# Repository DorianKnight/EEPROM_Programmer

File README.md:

# EEPROM_Programmer

## Project Overview
Custom Serializer Deserializer (SerDes) PCB designed to handle read/write operations to a parallel address EEPROM.

## High Level Architecture
Data from the host computer is transferred through serial communication to the Arduino. The Arduino writes the serial data into the SerDes which outputs the data in parallel to the EEPROM for storage.

To read information from the EEPROM, the Arduino loads the parallel data output into the SerDes and reconstructs the byte packet bit by bit. A high level functional block diagram explaining the system can be seen below.
.png)
.png)

## SerDes
A custom shift register functions as a primitive SerDes. Going from serial to parallel, the custom hardware allows serial data to ripple into individual flip-flops where each flip-flop drives an individual output. These outputs then wire into the EEPROM’s address and data pins. The same hardware also functions to load in the parallel data output from the EEPROM and shift it out sequentially such that the Arduino can reconstruct the byte packet.

## Debugging
To facilitate debugging operations, a debug daughter board PCB was constructed that allows the technician to manually toggle all control signals made available to the Arduino MCU.

## Motherboard Interface
The motherboard hosts a series of LEDs and seven-segment displays that serve to display the byte stored at a specific address. By changing the board to debug mode, the technician can select an address to read its binary and hexadecimal representation.

## Custom Bin -> Hex 7-SD Driver 
Binary to hexadecimal conversion was accomplished through the design of custom digital combinational logic that uses a series of primitive logic gates to turn a four bit binary input into a seven pin output. The individual outputs turn on or off the individual segments on a seven segment display.

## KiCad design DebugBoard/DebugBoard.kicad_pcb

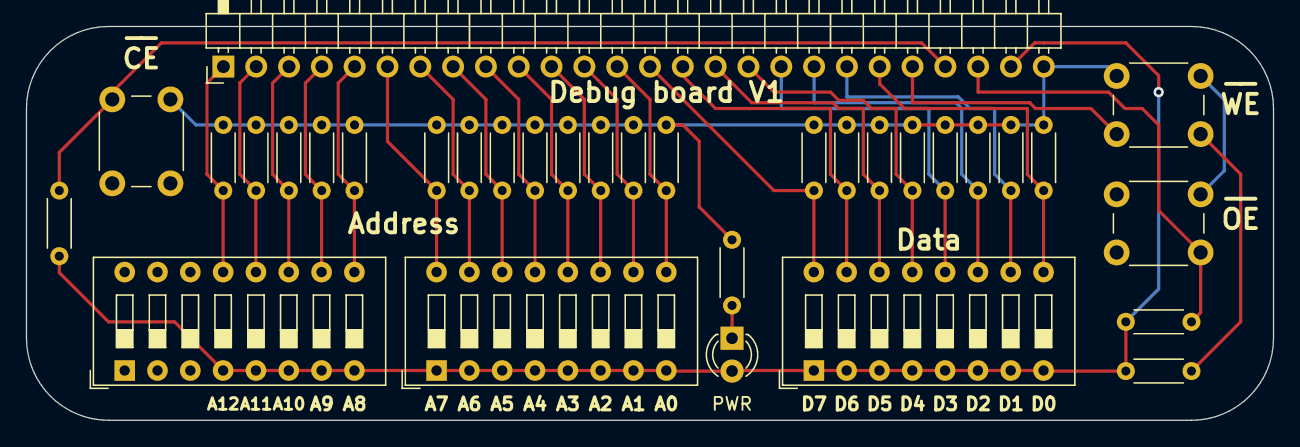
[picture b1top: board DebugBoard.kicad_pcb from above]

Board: 2 copper layers, 96.5 x 30.5 mm, 33 parts (0 on the bottom side), 27 nets.

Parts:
D1: LED; LED_D3.0mm_white
J1: Conn_01x26; PinHeader_1x26_P2.54mm_Horizontal
R1, R2, R3, R4, R5, R6, R7, R8, R9, R10, R11, R12, R13, R14, R15, R16, R17, R18, R19, R20, R21, R22, R23, R24, R25: R_US; R_Axial_DIN0204_L3.6mm_D1.6mm_P5.08mm_Horizontal
SW1, SW2, SW3: SW_DIP_x08; SW_DIP_SPSTx08_Slide_9.78x22.5mm_W7.62mm_P2.54mm
SW4, SW5, SW6: SW_Push; SW_PUSH_6mm

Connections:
A0: J1.13, R24.1, SW3.9
A1: J1.12, R23.1, SW3.10
A2: J1.11, R22.1, SW3.11
A3: J1.10, R21.1, SW3.12
A4: J1.9, R20.1, SW3.13
A5: J1.8, R19.1, SW3.14
A6: J1.7, R18.1, SW3.15
A7: J1.6, R17.1, SW3.16
A8: J1.5, R16.1, SW2.9
A9: J1.4, R15.1, SW2.10
A10: J1.3, R14.1, SW2.11
A11: J1.2, R13.1, SW2.12
A12: J1.1, R12.1, SW2.13
CE': J1.23, R5.2, SW5.2
D0: J1.21, R11.1, SW1.9
D1: J1.20, R10.1, SW1.10
D2: J1.19, R9.1, SW1.11
D3: J1.18, R8.1, SW1.12
D4: J1.17, R6.1, SW1.13
D5: J1.16, R4.1, SW1.14
D6: J1.15, R2.1, SW1.15
D7: J1.14, R1.1, SW1.16
GND: J1.26, R1.2, R2.2, R4.2, R6.2, R8.2, R9.2, R10.2, R11.2, R12.2, R13.2, R14.2, R15.2, R16.2, R17.2, R18.2, R19.2, R20.2, R21.2, R22.2, R23.2, R24.2, R25.1, SW4.1, SW5.1, SW6.1
unnamed: D1.1 (K), R25.2
OE': J1.24, R3.2, SW6.2
VCC: D1.2 (A), J1.25, R3.1, R5.1, R7.1, SW1.1, SW1.2, SW1.3, SW1.4, SW1.5, SW1.6, SW1.7, SW1.8, SW2.4, SW2.5, SW2.6, SW2.7, SW2.8, SW3.1, SW3.2, SW3.3, SW3.4, SW3.5, SW3.6, SW3.7, SW3.8
WE': J1.22, R7.2, SW4.2

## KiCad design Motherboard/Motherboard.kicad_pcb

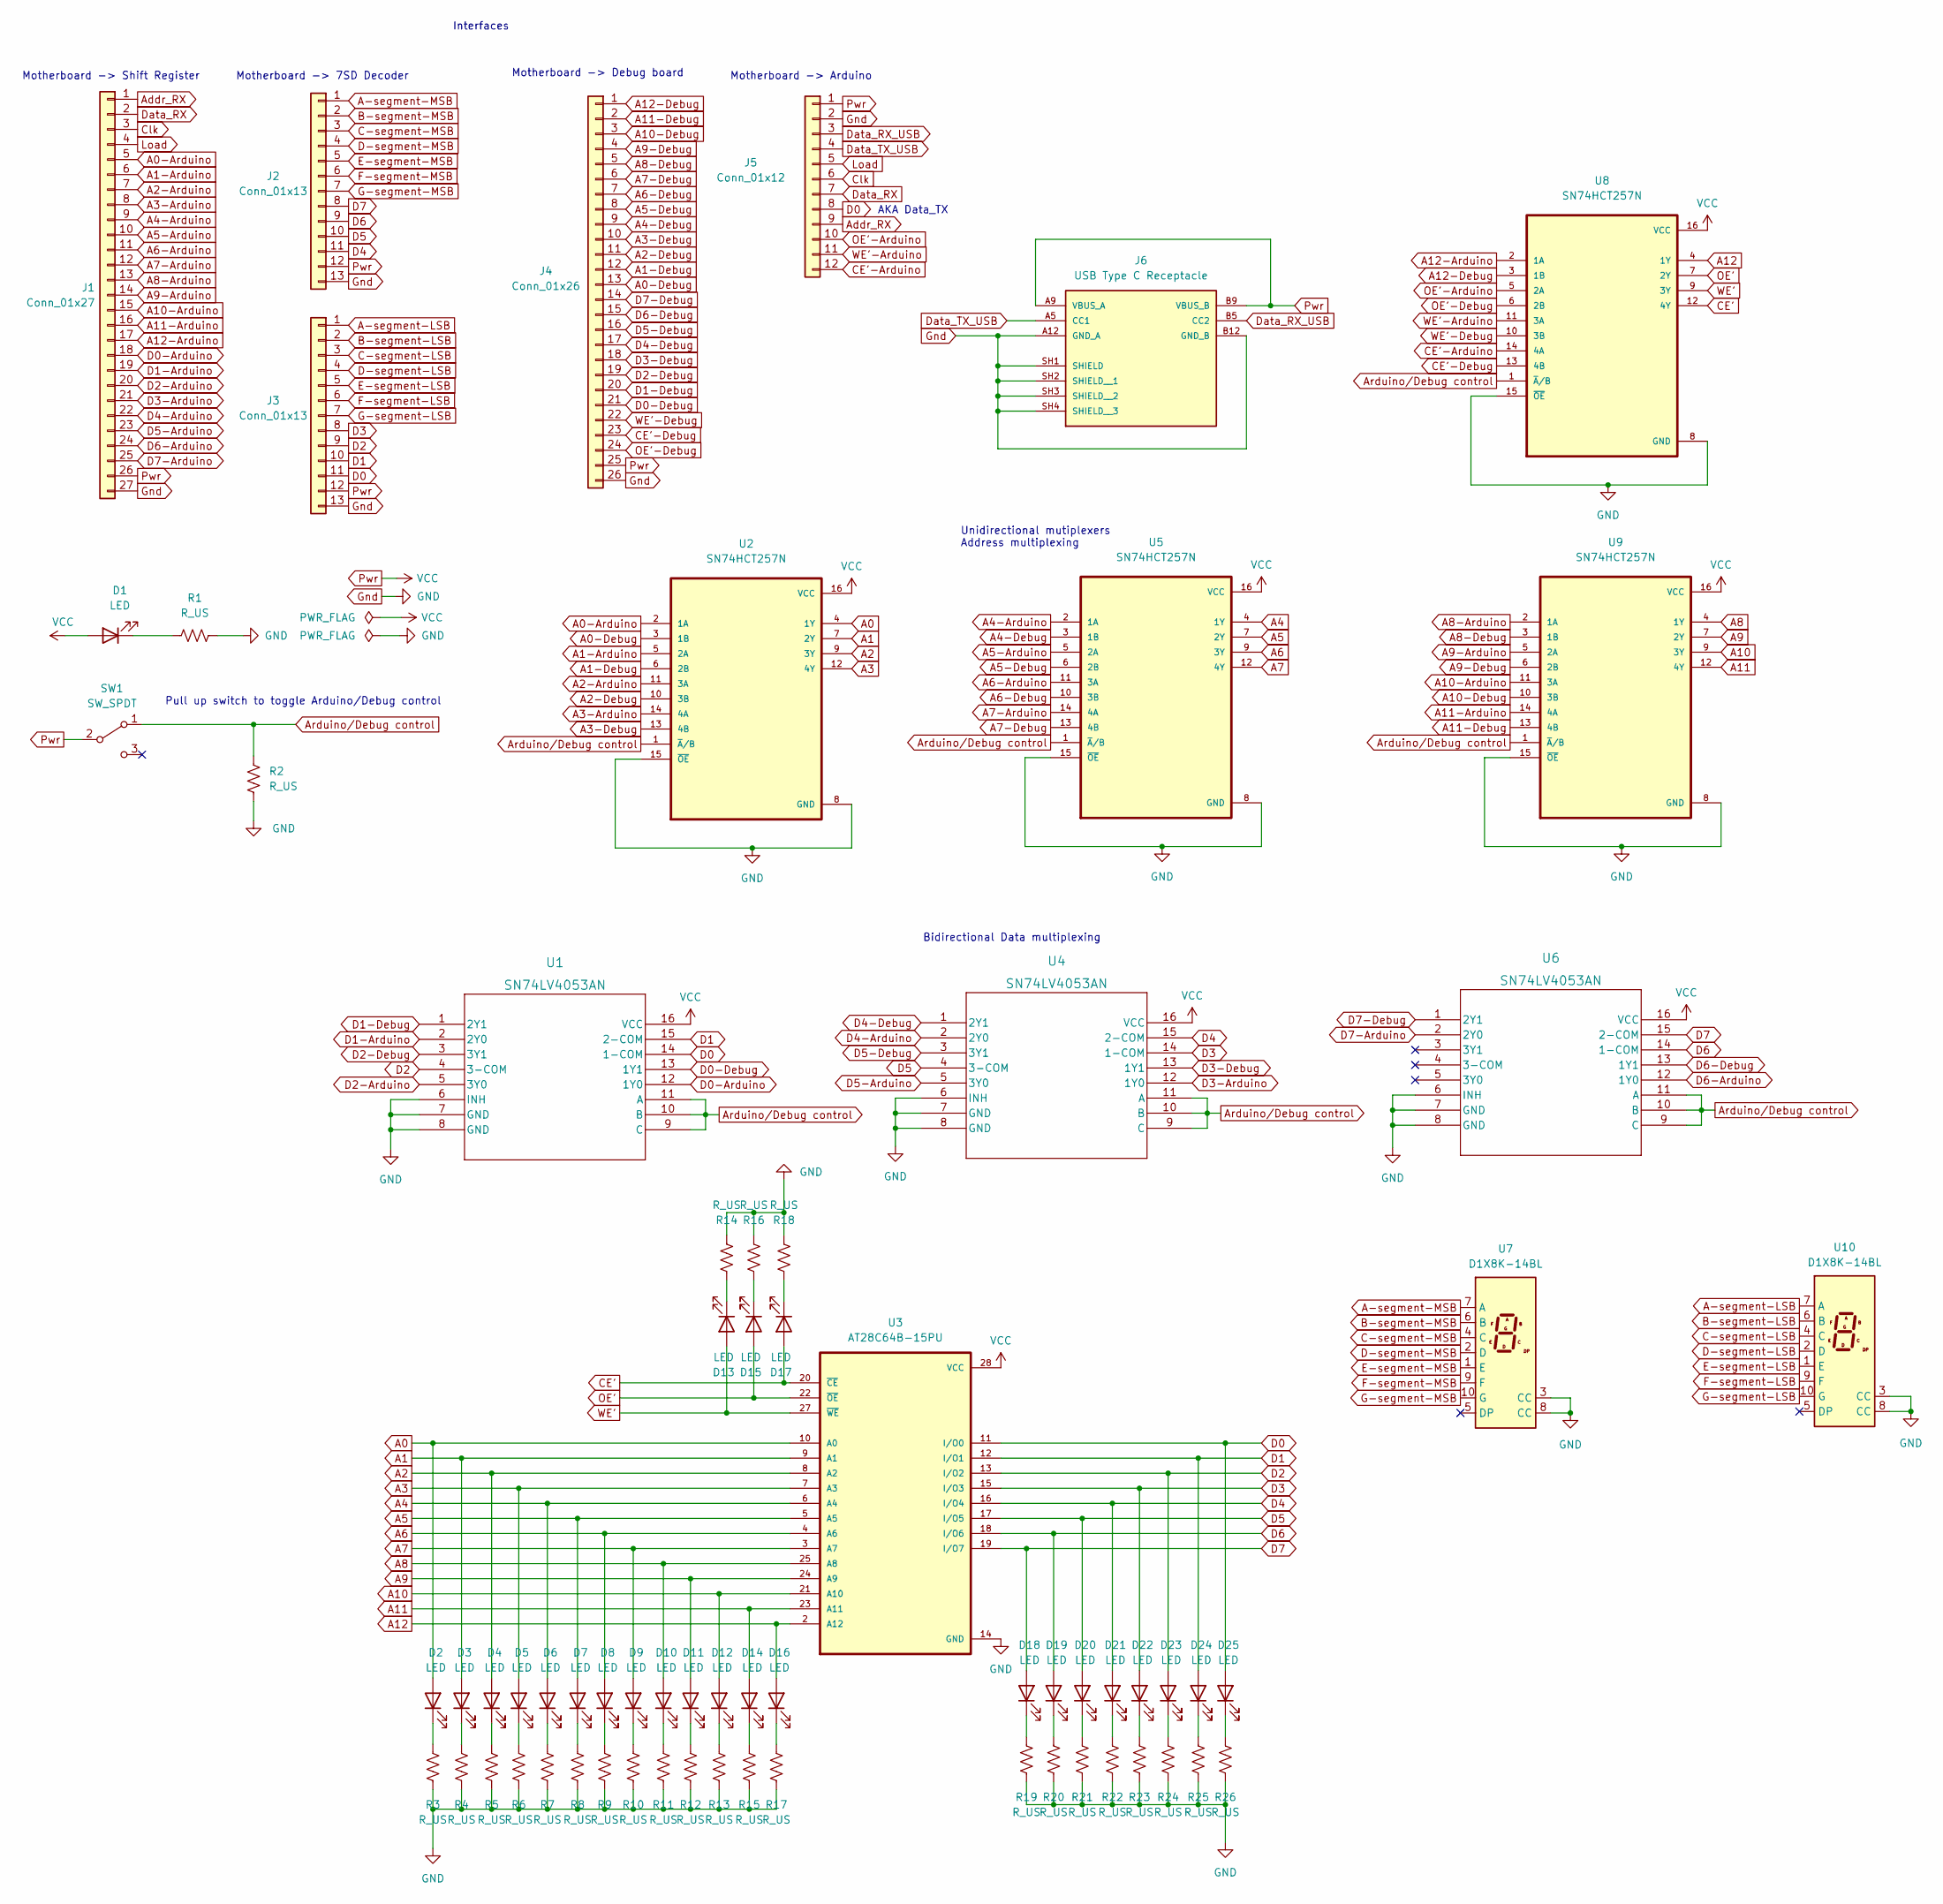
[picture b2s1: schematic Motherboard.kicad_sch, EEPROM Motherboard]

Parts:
D1: LED; LED_D3.0mm_red
D2, D3, D4, D5, D6, D7, D8, D9, D10, D11, D12, D14, D16: LED; LED_D3.0mm_blue
D13, D15, D17: LED; LED_D3.0mm_yellow
D18, D19, D20, D21, D22, D23, D24, D25: LED; LED_D3.0mm_white
J1: Conn_01x27; PinSocket_1x27_P2.54mm_Horizontal
J2, J3: Conn_01x13; PinSocket_1x13_P2.54mm_Horizontal
J4: Conn_01x26; PinSocket_1x26_P2.54mm_Horizontal
J5: Conn_01x12; PinSocket_1x12_P2.54mm_Horizontal
J6: USB Type C Receptacle; AMPHENOL_10164359-00011LF; PARTREV A
R1, R2, R3, R4, R5, R6, R7, R8, R9, R10, R11, R12, R13, R14, R15, R16, R17, R18, R19, R20, R21, R22, R23, R24, R25, R26: R_US; R_Axial_DIN0204_L3.6mm_D1.6mm_P5.08mm_Horizontal
SW1: SW_SPDT; SPDT_SW_SLW-116641-5A-S-D
U1, U4, U6: SN74LV4053AN
U2, U5, U8, U9: SN74HCT257N; DIP794W45P254L1969H508Q16
U3: AT28C64B-15PU; EEPROM in 40pin ZIF; PARTREV B
U7, U10: D1X8K-14BL; D1X8K

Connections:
A0: D2.2 (A), U2.4 (1Y), U3.10 (A0)
A0-Arduino: J1.5, U2.2 (1A)
A0-Debug: J4.13, U2.3 (1B)
A1: D3.2 (A), U2.7 (2Y), U3.9 (A1)
A1-Arduino: J1.6, U2.5 (2A)
A1-Debug: J4.12, U2.6 (2B)
A2: D4.2 (A), U2.9 (3Y), U3.8 (A2)
A2-Arduino: J1.7, U2.11 (3A)
A2-Debug: J4.11, U2.10 (3B)
A3: D5.2 (A), U2.12 (4Y), U3.7 (A3)
A3-Arduino: J1.8, U2.14 (4A)
A3-Debug: J4.10, U2.13 (4B)
A4: D6.2 (A), U3.6 (A4), U5.4 (1Y)
A4-Arduino: J1.9, U5.2 (1A)
A4-Debug: J4.9, U5.3 (1B)
A5: D7.2 (A), U3.5 (A5), U5.7 (2Y)
A5-Arduino: J1.10, U5.5 (2A)
A5-Debug: J4.8, U5.6 (2B)
A6: D8.2 (A), U3.4 (A6), U5.9 (3Y)
A6-Arduino: J1.11, U5.11 (3A)
A6-Debug: J4.7, U5.10 (3B)
A7: D9.2 (A), U3.3 (A7), U5.12 (4Y)
A7-Arduino: J1.12, U5.14 (4A)
A7-Debug: J4.6, U5.13 (4B)
A8: D10.2 (A), U3.25 (A8), U9.4 (1Y)
A8-Arduino: J1.13, U9.2 (1A)
A8-Debug: J4.5, U9.3 (1B)
A9: D11.2 (A), U3.24 (A9), U9.7 (2Y)
A9-Arduino: J1.14, U9.5 (2A)
A9-Debug: J4.4, U9.6 (2B)
A10: D12.2 (A), U3.21 (A10), U9.9 (3Y)
A10-Arduino: J1.15, U9.11 (3A)
A10-Debug: J4.3, U9.10 (3B)
A11: D14.2 (A), U3.23 (A11), U9.12 (4Y)
A11-Arduino: J1.16, U9.14 (4A)
A11-Debug: J4.2, U9.13 (4B)
A12: D16.2 (A), U3.2 (A12), U8.4 (1Y)
A12-Arduino: J1.17, U8.2 (1A)
A12-Debug: J4.1, U8.3 (1B)
A-segment-LSB: J3.1, U10.7 (A)
A-segment-MSB: J2.1, U7.7 (A)
Addr_RX: J1.1, J5.9
Arduino/Debug control: R2.1, SW1.1 (A), U1.9 (C), U1.10 (B), U1.11 (A), U2.1 (~A/B), U4.9 (C), U4.10 (B), U4.11 (A), U5.1 (~A/B), U6.9 (C), U6.10 (B), U6.11 (A), U8.1 (~A/B), U9.1 (~A/B)
B-segment-LSB: J3.2, U10.6 (B)
B-segment-MSB: J2.2, U7.6 (B)
C-segment-LSB: J3.3, U10.4 (C)
C-segment-MSB: J2.3, U7.4 (C)
CE': D17.2 (A), U3.20 (~CE), U8.12 (4Y)
CE'-Arduino: J5.12, U8.14 (4A)
CE'-Debug: J4.23, U8.13 (4B)
Clk: J1.3, J5.6
D0: D25.2 (A), J3.11, J5.8, U1.14 (1-COM), U3.11 (I/O0)
D0-Arduino: J1.18, U1.12 (1Y0)
D0-Debug: J4.21, U1.13 (1Y1)
D1: D24.2 (A), J3.10, U1.15 (2-COM), U3.12 (I/O1)
D1-Arduino: J1.19, U1.2 (2Y0)
D1-Debug: J4.20, U1.1 (2Y1)
D2: D23.2 (A), J3.9, U1.4 (3-COM), U3.13 (I/O2)
D2-Arduino: J1.20, U1.5 (3Y0)
D2-Debug: J4.19, U1.3 (3Y1)
D3: D22.2 (A), J3.8, U3.15 (I/O3), U4.14 (1-COM)
D3-Arduino: J1.21, U4.12 (1Y0)
D3-Debug: J4.18, U4.13 (1Y1)
D4: D21.2 (A), J2.11, U3.16 (I/O4), U4.15 (2-COM)
D4-Arduino: J1.22, U4.2 (2Y0)
D4-Debug: J4.17, U4.1 (2Y1)
D5: D20.2 (A), J2.10, U3.17 (I/O5), U4.4 (3-COM)
D5-Arduino: J1.23, U4.5 (3Y0)
D5-Debug: J4.16, U4.3 (3Y1)
D6: D19.2 (A), J2.9, U3.18 (I/O6), U6.14 (1-COM)
D6-Arduino: J1.24, U6.12 (1Y0)
D6-Debug: J4.15, U6.13 (1Y1)
D7: D18.2 (A), J2.8, U3.19 (I/O7), U6.15 (2-COM)
D7-Arduino: J1.25, U6.2 (2Y0)
D7-Debug: J4.14, U6.1 (2Y1)
D-segment-LSB: J3.4, U10.2 (D)
D-segment-MSB: J2.4, U7.2 (D)
Data_RX: J1.2, J5.7
Data_RX_USB: J5.3, J6.B5 (CC2)
Data_TX_USB: J5.4, J6.A5 (CC1)
E-segment-LSB: J3.5, U10.1 (E)
E-segment-MSB: J2.5, U7.1 (E)
F-segment-LSB: J3.6, U10.9 (F)
F-segment-MSB: J2.6, U7.9 (F)
G-segment-LSB: J3.7, U10.10 (G)
G-segment-MSB: J2.7, U7.10 (G)
Gnd: J1.27, J2.13, J3.13, J4.26, J5.2, J6.A12 (GND_A), J6.B12 (GND_B), J6.SH1 (SHIELD), J6.SH2 (SHIELD__1), J6.SH3 (SHIELD__2), J6.SH4 (SHIELD__3), R1.1, R2.2, R3.1, R4.1, R5.1, R6.1, R7.1, R8.1, R9.1, R10.1, R11.1, R12.1, R13.1, R14.1, R15.1, R16.1, R17.1, R18.1, R19.1, R20.1, R21.1, R22.1, R23.1, R24.1, R25.1, R26.1, U1.6 (INH), U1.7 (GND), U1.8 (GND), U2.8 (GND), U2.15 (~OE), U3.14 (GND), U4.6 (INH), U4.7 (GND), U4.8 (GND), U5.8 (GND), U5.15 (~OE), U6.6 (INH), U6.7 (GND), U6.8 (GND), U7.3 (CC), U7.8 (CC), U8.8 (GND), U8.15 (~OE), U9.8 (GND), U9.15 (~OE), U10.3 (CC), U10.8 (CC)
Load: J1.4, J5.5
unnamed: D1.1 (K), R1.2
unnamed: D2.1 (K), R3.2
unnamed: D3.1 (K), R4.2
unnamed: D4.1 (K), R5.2
unnamed: D5.1 (K), R6.2
unnamed: D6.1 (K), R7.2
unnamed: D7.1 (K), R8.2
unnamed: D8.1 (K), R9.2
unnamed: D9.1 (K), R10.2
unnamed: D10.1 (K), R11.2
unnamed: D11.1 (K), R12.2
unnamed: D12.1 (K), R13.2
unnamed: D13.1 (K), R14.2
unnamed: D14.1 (K), R15.2
unnamed: D15.1 (K), R16.2
unnamed: D16.1 (K), R17.2
unnamed: D17.1 (K), R18.2
unnamed: D18.1 (K), R19.2
unnamed: D19.1 (K), R20.2
unnamed: D20.1 (K), R21.2
unnamed: D21.1 (K), R22.2
unnamed: D22.1 (K), R23.2
unnamed: D23.1 (K), R24.2
unnamed: D24.1 (K), R25.2
unnamed: D25.1 (K), R26.2
OE': D15.2 (A), U3.22 (~OE), U8.7 (2Y)
OE'-Arduino: J5.10, U8.5 (2A)
OE'-Debug: J4.24, U8.6 (2B)
Pwr: D1.2 (A), J1.26, J2.12, J3.12, J4.25, J5.1, J6.A9 (VBUS_A), J6.B9 (VBUS_B), SW1.2 (B), U1.16 (VCC), U2.16 (VCC), U3.28 (VCC), U4.16 (VCC), U5.16 (VCC), U6.16 (VCC), U8.16 (VCC), U9.16 (VCC)
WE': D13.2 (A), U3.27 (~WE), U8.9 (3Y)
WE'-Arduino: J5.11, U8.11 (3A)
WE'-Debug: J4.22, U8.10 (3B)

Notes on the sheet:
Bidirectional Data multiplexing
Motherboard -> 7SD Decoder
Pull up switch to toggle Arduino/Debug control
Motherboard -> Shift Register
Motherboard -> Arduino
Interfaces
Unidirectional mutiplexers Address multiplexing
AKA Data_TX
Motherboard -> Debug board

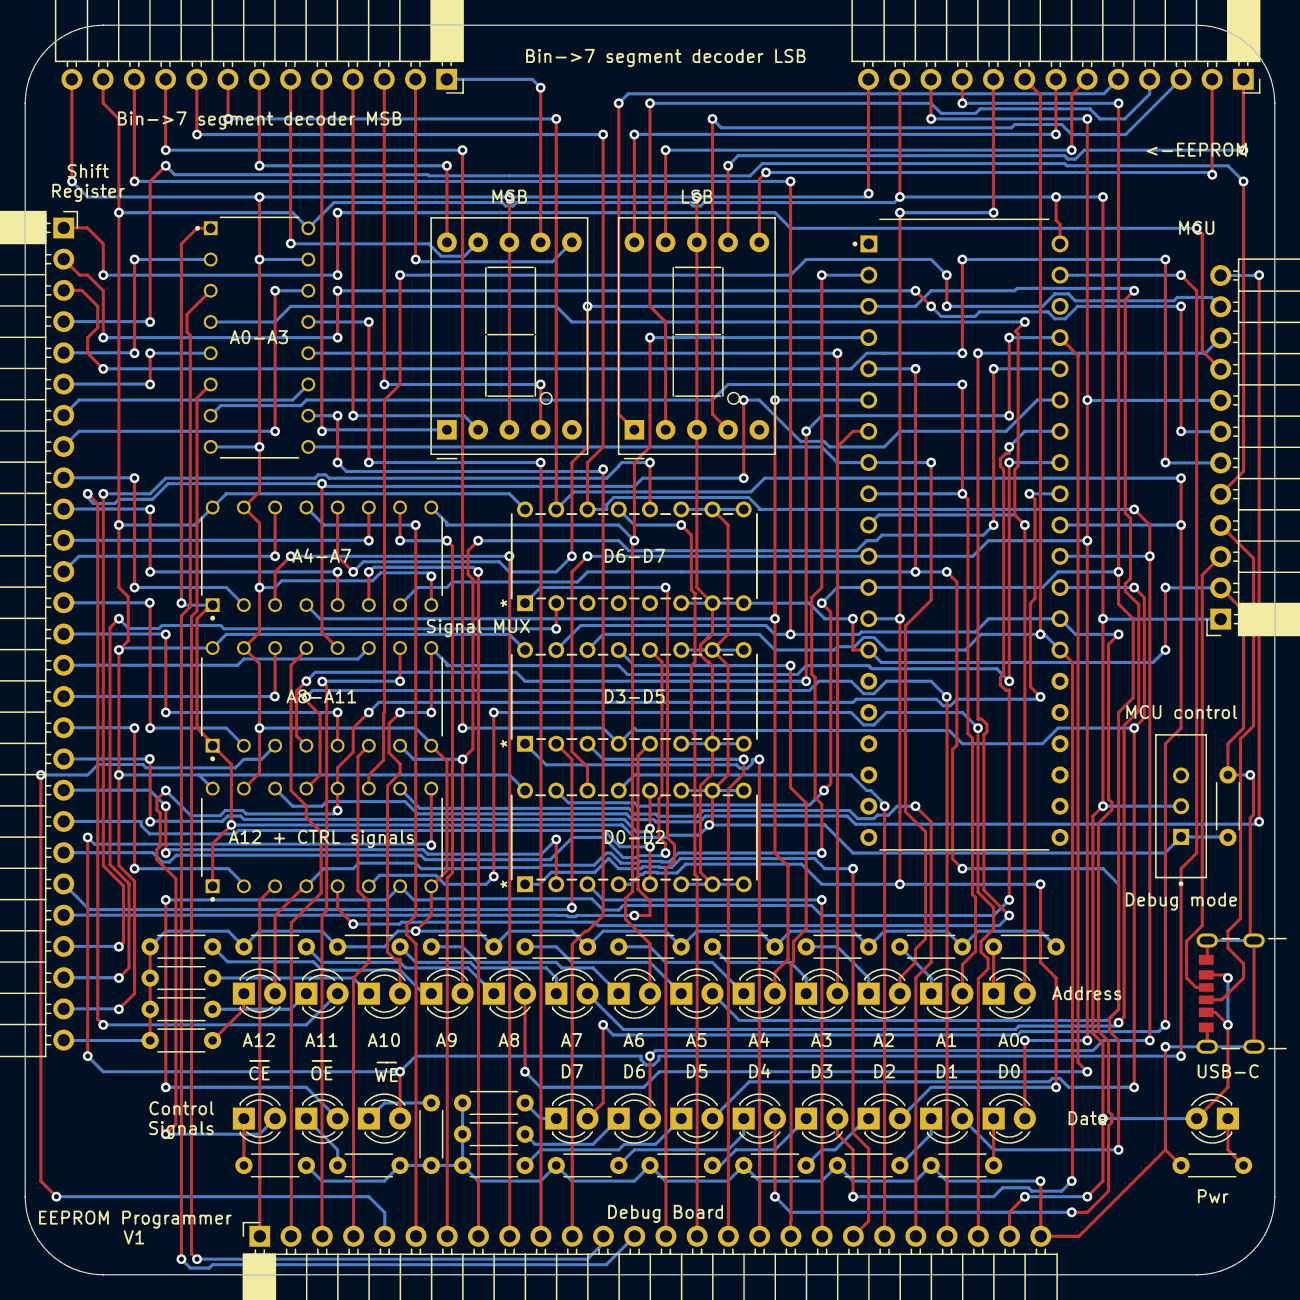
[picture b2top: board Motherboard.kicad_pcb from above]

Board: 2 copper layers, 101.6 x 101.6 mm, 68 parts (0 on the bottom side), 120 nets.

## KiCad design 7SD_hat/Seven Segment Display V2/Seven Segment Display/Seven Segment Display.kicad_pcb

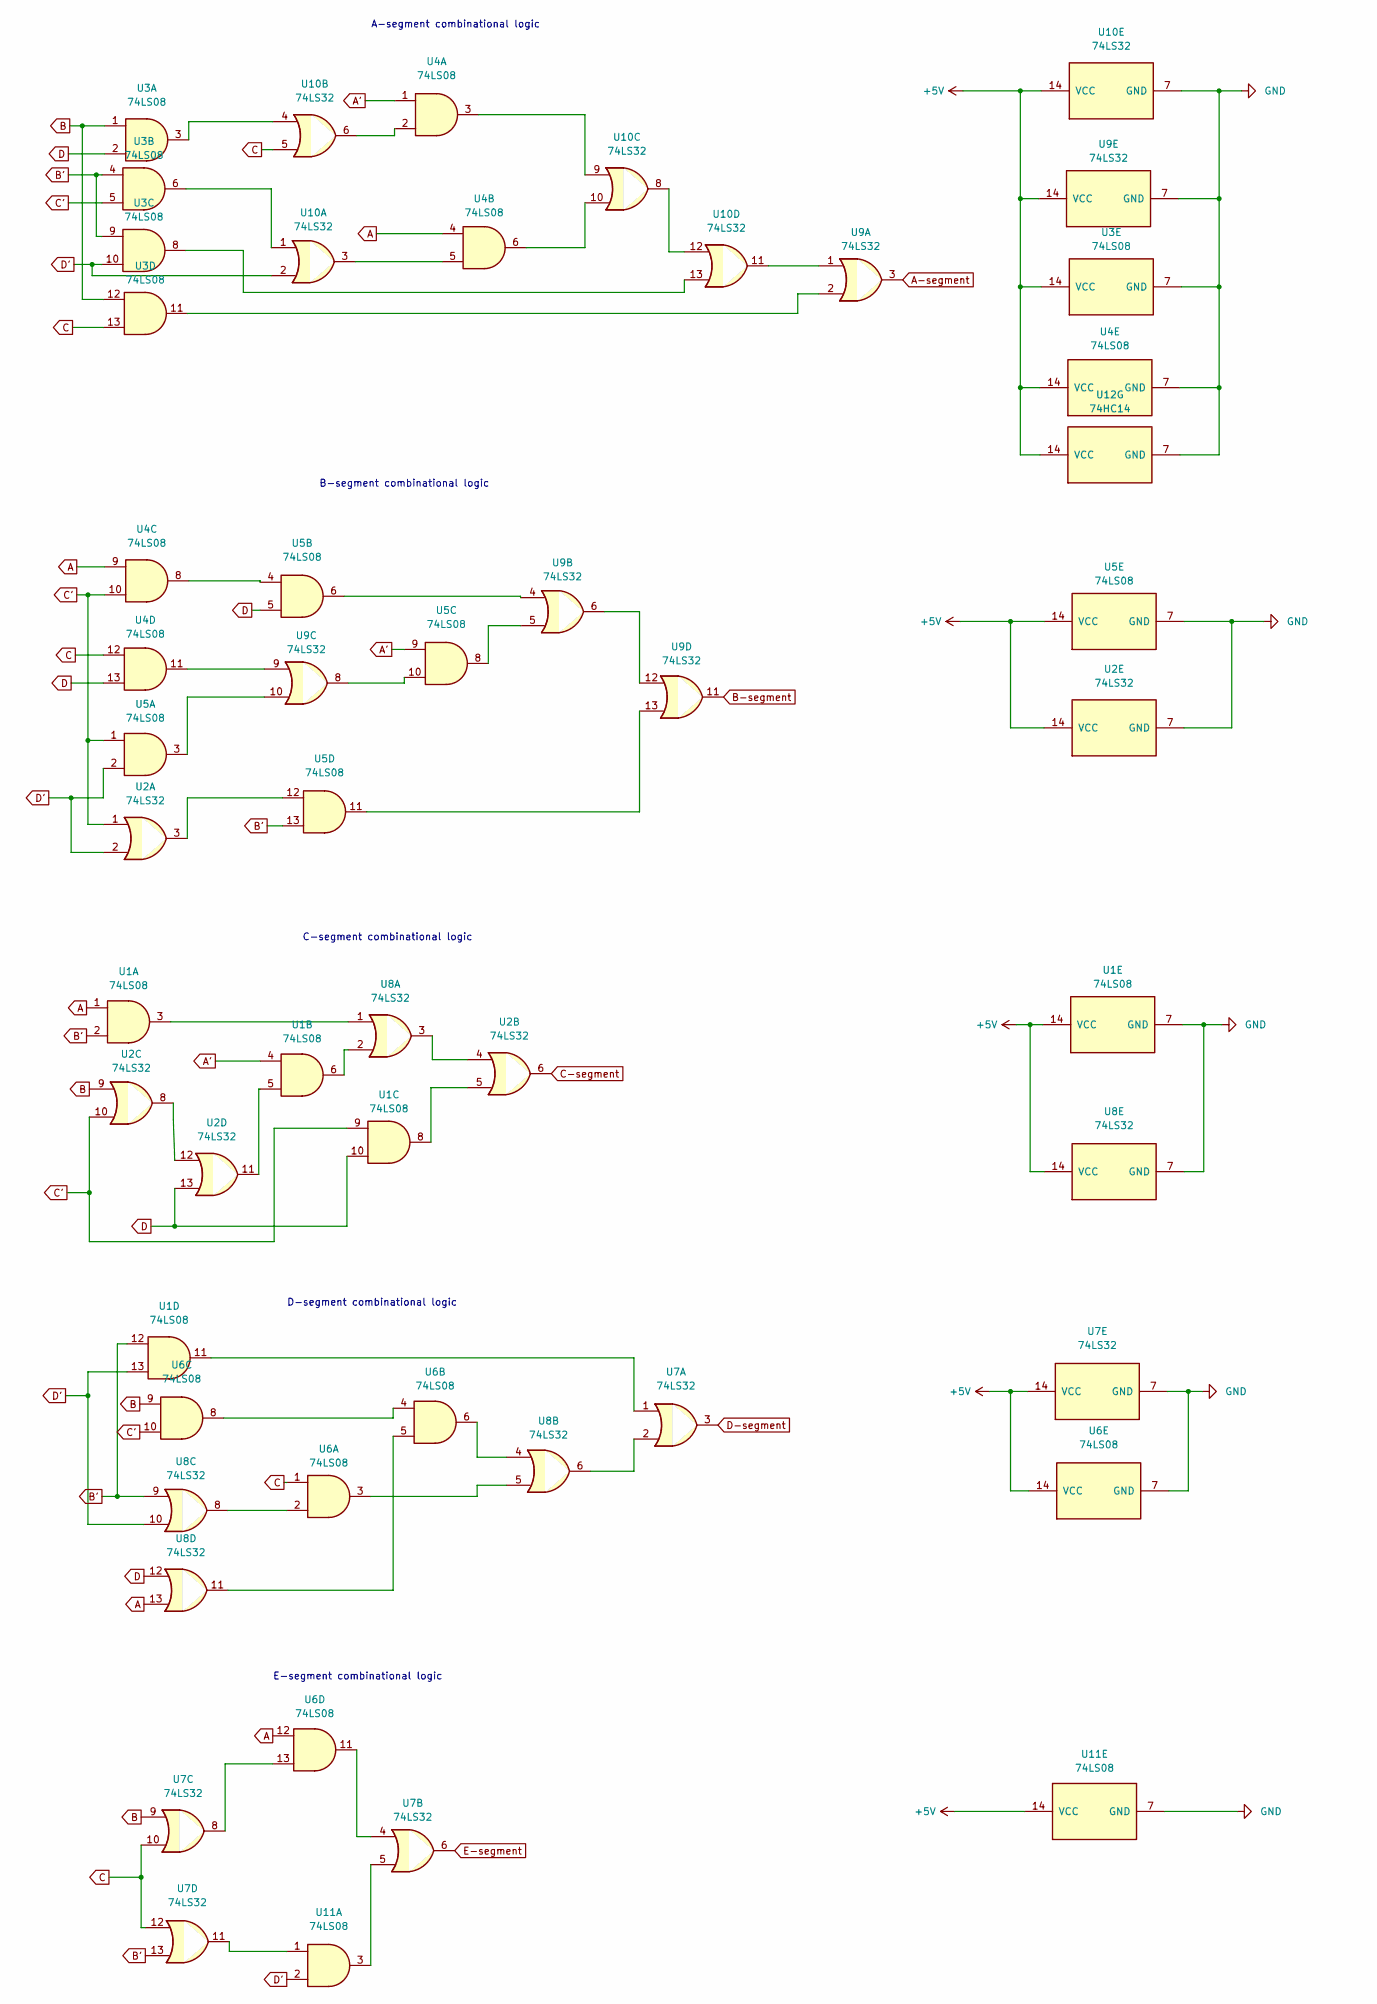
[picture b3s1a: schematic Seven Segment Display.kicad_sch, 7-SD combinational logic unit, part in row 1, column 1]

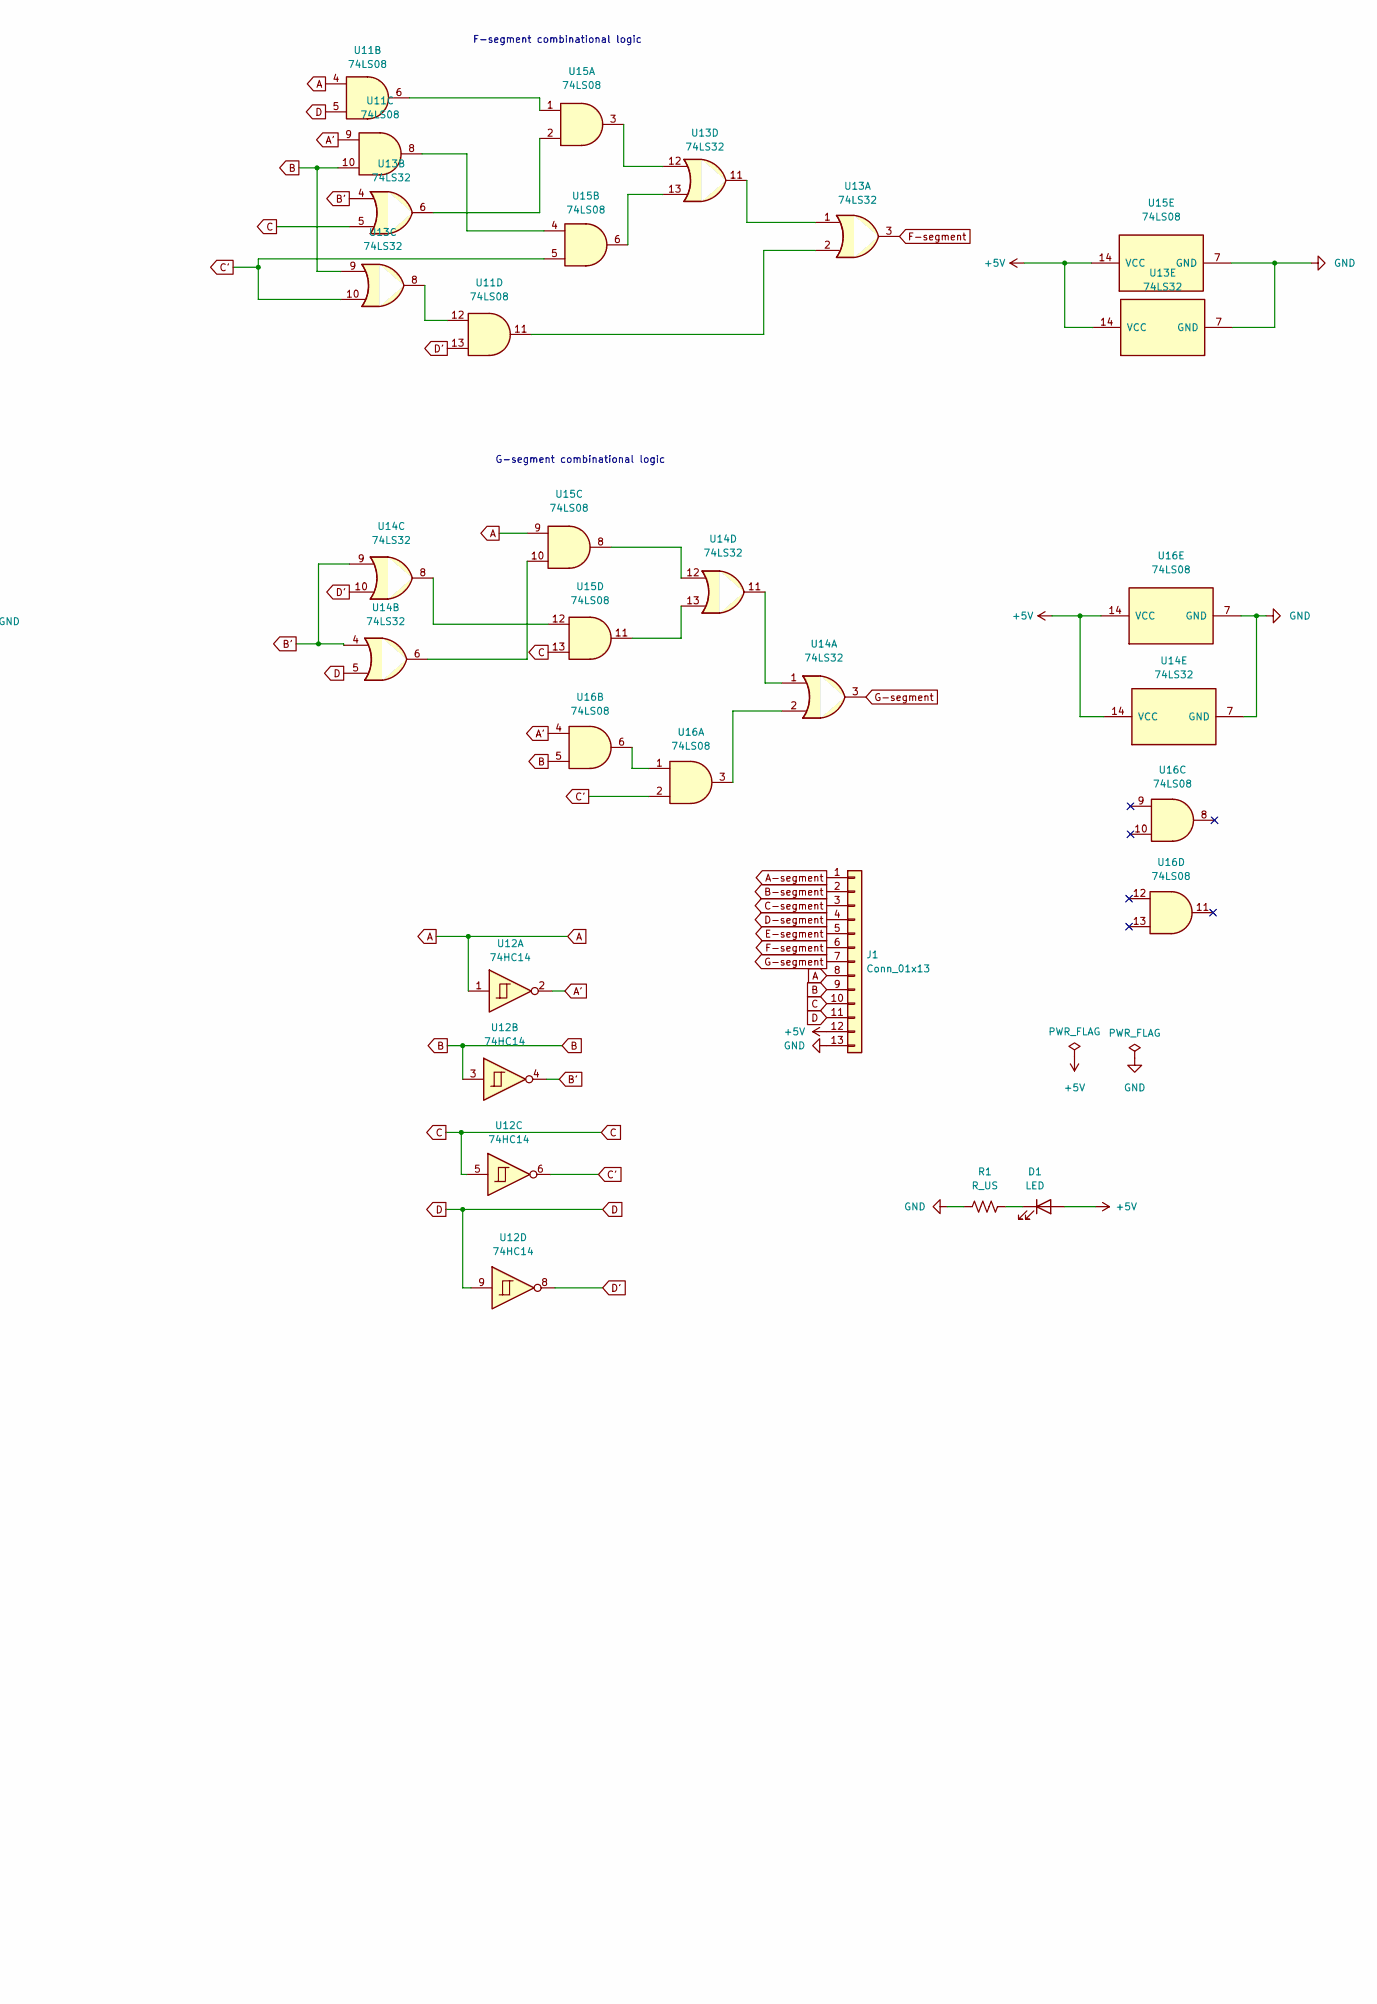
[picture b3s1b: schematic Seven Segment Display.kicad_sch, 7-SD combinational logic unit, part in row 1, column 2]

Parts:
D1: LED; LED_D3.0mm_red
J1: Conn_01x13; PinHeader_1x13_P2.54mm_Horizontal
R1: R_US; R_Axial_DIN0204_L3.6mm_D1.6mm_P5.08mm_Horizontal
U1, U3, U4, U5, U6, U11, U15, U16: 74LS08; DIP-14_W7.62mm
U2, U7, U8, U9, U10, U13, U14: 74LS32; DIP-14_W7.62mm
U12: 74HC14; DIP-14_W7.62mm

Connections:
+5V: D1.2 (A), J1.12, U1.14 (VCC), U2.14 (VCC), U3.14 (VCC), U4.14 (VCC), U5.14 (VCC), U6.14 (VCC), U7.14 (VCC), U8.14 (VCC), U9.14 (VCC), U10.14 (VCC), U11.14 (VCC), U12.14 (VCC), U13.14 (VCC), U14.14 (VCC), U15.14 (VCC), U16.14 (VCC)
A: J1.8, U1.1, U4.4, U4.9, U6.12, U8.13, U11.4, U12.1, U15.9
A': U1.4, U4.1, U5.9, U11.9, U12.2, U16.4
A-segment: J1.1, U9.3
B: J1.9, U2.9, U3.1, U3.12, U6.9, U7.9, U11.10, U12.3, U13.9, U16.5
B': U1.2, U1.12, U3.4, U3.9, U5.13, U7.13, U8.9, U12.4, U13.4, U14.4, U14.9
B-segment: J1.2, U9.11
C: J1.10, U3.13, U4.12, U6.1, U7.10, U7.12, U10.5, U12.5, U13.5, U15.13
C': U1.9, U2.1, U2.10, U3.5, U4.10, U5.1, U6.10, U12.6, U13.10, U15.5, U16.2
C-segment: J1.3, U2.6
D: J1.11, U1.10, U2.13, U3.2, U4.13, U5.5, U8.12, U11.5, U12.9, U14.5
D': U1.13, U2.2, U3.10, U5.2, U8.10, U10.2, U11.2, U11.13, U12.8, U14.10
D-segment: J1.4, U7.3
E-segment: J1.5, U7.6
F-segment: J1.6, U13.3
G-segment: J1.7, U14.3
GND: J1.13, R1.1, U1.7 (GND), U2.7 (GND), U3.7 (GND), U4.7 (GND), U5.7 (GND), U6.7 (GND), U7.7 (GND), U8.7 (GND), U9.7 (GND), U10.7 (GND), U11.7 (GND), U12.7 (GND), U13.7 (GND), U14.7 (GND), U15.7 (GND), U16.7 (GND)
unnamed: D1.1 (K), R1.2
unnamed: U1.3, U8.1
unnamed: U1.5, U2.11
unnamed: U1.6, U8.2
unnamed: U1.8, U2.5
unnamed: U1.11, U7.1
unnamed: U2.3, U5.12
unnamed: U2.4, U8.3
unnamed: U2.8, U2.12
unnamed: U3.11, U9.2
unnamed: U4.8, U5.4
unnamed: U4.11, U9.9
unnamed: U5.3, U9.10
unnamed: U5.6, U9.4
unnamed: U5.8, U9.5
unnamed: U5.10, U9.8
unnamed: U5.11, U9.13
unnamed: U6.2, U8.8
unnamed: U6.3, U8.5
unnamed: U6.4, U6.8
unnamed: U6.5, U8.11
unnamed: U6.6, U8.4
unnamed: U6.11, U7.4
unnamed: U6.13, U7.8
unnamed: U7.2, U8.6
unnamed: U9.6, U9.12
unnamed: U3.6, U10.1
unnamed: U4.5, U10.3
unnamed: U3.3, U10.4
unnamed: U4.2, U10.6
unnamed: U4.3, U10.9
unnamed: U4.6, U10.10
unnamed: U9.1, U10.11
unnamed: U10.8, U10.12
unnamed: U3.8, U10.13
unnamed: U7.11, U11.1
unnamed: U7.5, U11.3
unnamed: U11.6, U15.1
unnamed: U11.8, U15.4
unnamed: U11.11, U13.2
unnamed: U11.12, U13.8
unnamed: U13.1, U13.11
unnamed: U13.6, U15.2
unnamed: U13.12, U15.3
unnamed: U13.13, U15.6
unnamed: U14.1, U14.11
unnamed: U14.2, U16.3
unnamed: U14.6, U15.10
unnamed: U14.8, U15.12
unnamed: U14.12, U15.8
unnamed: U14.13, U15.11
unnamed: U16.1, U16.6

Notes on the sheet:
D-segment combinational logic
G-segment combinational logic
A-segment combinational logic
F-segment combinational logic
B-segment combinational logic
C-segment combinational logic
E-segment combinational logic

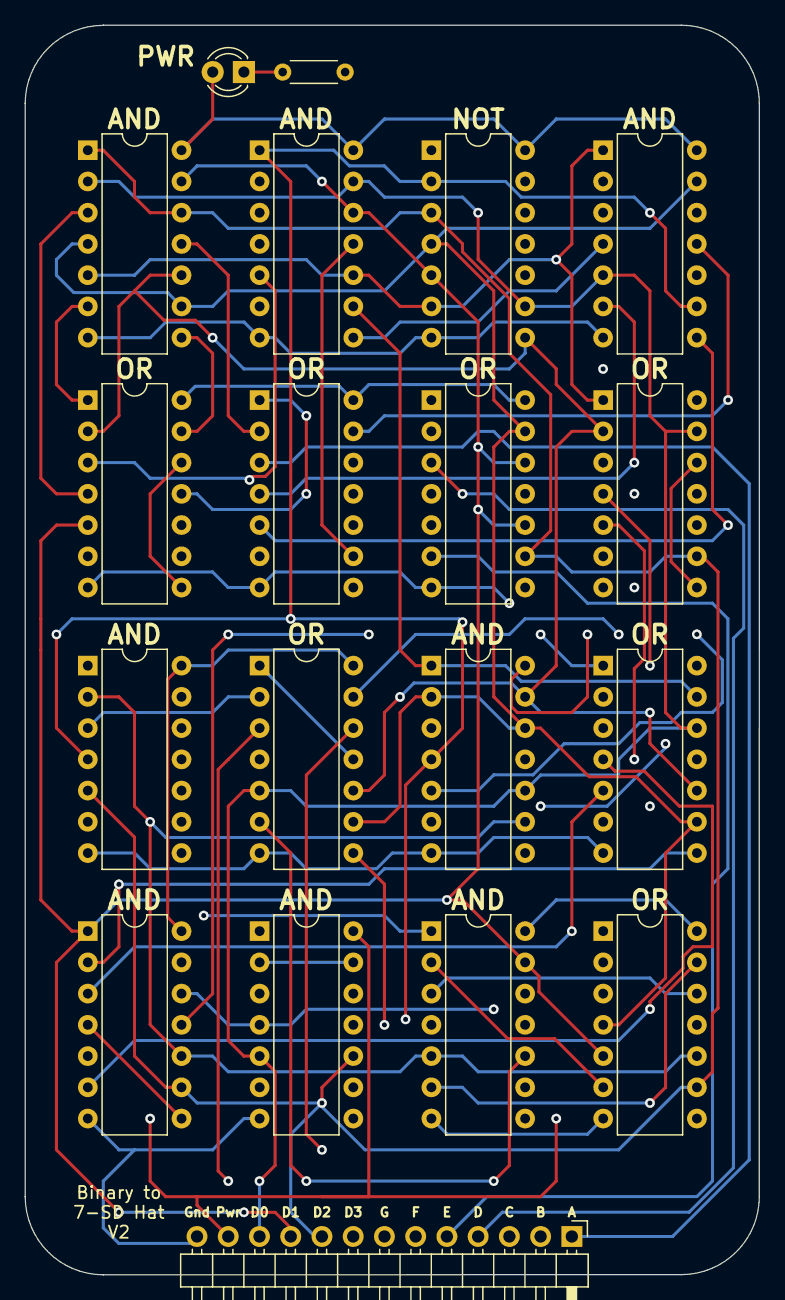
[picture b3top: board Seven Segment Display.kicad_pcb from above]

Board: 4 copper layers, 59.7 x 101.6 mm, 19 parts (0 on the bottom side), 69 nets.
